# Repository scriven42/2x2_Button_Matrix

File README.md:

# 2x2_Button_Matrix

NB: I found a bug where the schematic I was using for the button was wrong, so, don't get this one yet.

As part of an ongoing project I'm not yet ready to release on here, I was looking for basic button boards I could use. And while there are several, they didn't
look like I had pictured and I didn't think they'd be comfortable to hold or use as a control. They were mostly square, and I couldn't tell the quality of the buttons
themselves or the circuitry used.

So I designed my own. It includes diodes and small capacitors for each button, to properly distinguish between buttons and allow chording.

When the code is ready to release, I'll update this to include a sample.

---
[*CC BY-SA 4.0*](https://creativecommons.org/licenses/by-sa/4.0/)

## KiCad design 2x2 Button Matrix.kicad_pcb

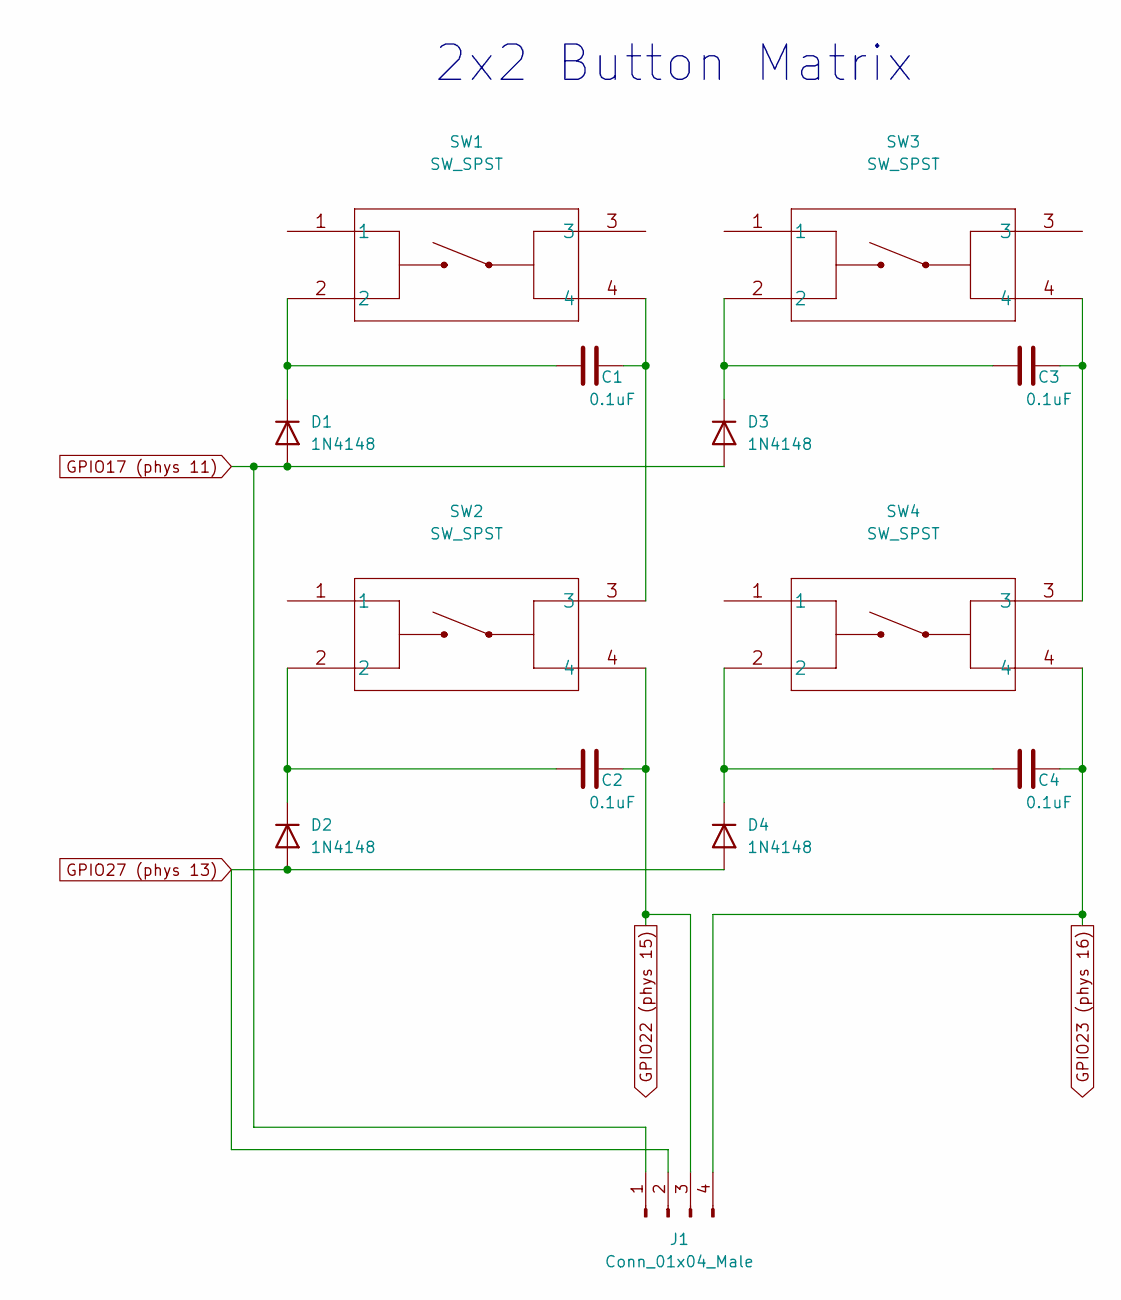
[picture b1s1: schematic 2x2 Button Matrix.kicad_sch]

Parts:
C1, C2, C3, C4: 0.1uF; C_0402_1005Metric
D1, D2, D3, D4: 1N4148; D_SOD-523
J1: Conn_01x04_Male; PinHeader_1x04_P2.54mm_Vertical
SW1, SW2, SW3, SW4: SW_SPST; 222JMVABR; MPN 222JMVABR

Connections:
GPIO17 (phys 11): D1.2 (A), D3.2 (A), J1.1
GPIO22 (phys 15): C2.2, J1.3, SW2.4
GPIO23 (phys 16): C4.2, J1.4, SW4.4
GPIO27 (phys 13): D2.2 (A), D4.2 (A), J1.2
unnamed: C1.1, D1.1 (K), SW1.2
unnamed: C1.2, SW1.4, SW2.3
unnamed: C2.1, D2.1 (K), SW2.2
unnamed: C3.1, D3.1 (K), SW3.2
unnamed: C3.2, SW3.4, SW4.3
unnamed: C4.1, D4.1 (K), SW4.2

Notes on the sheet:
2x2 Button Matrix

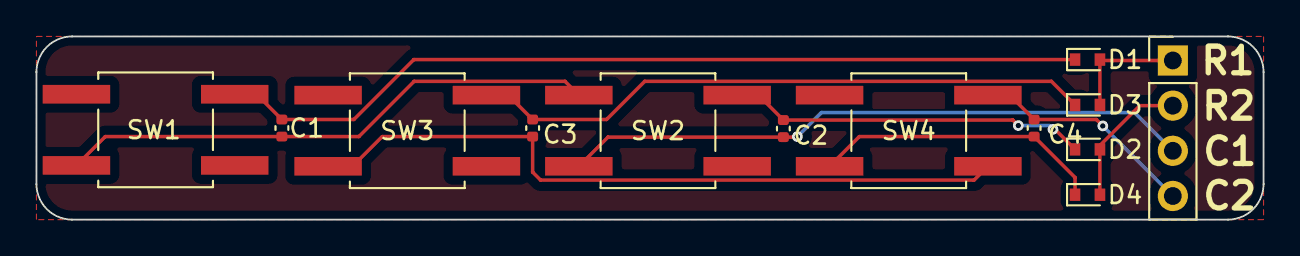
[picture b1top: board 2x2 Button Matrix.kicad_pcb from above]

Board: 2 copper layers, 69.0 x 10.3 mm, 13 parts (0 on the bottom side), 10 nets.

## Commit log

2022-07-01 Initial git commit.
2022-07-01 Added Readme.md file
2022-07-02 Added a link to the Aisler.net project
2022-07-02 Added a link to the PCBway project
2022-07-03 Update README.md
    Added link to the Creative Commons explanation
2022-07-17 Update README.md
    Found a bug in the schematic, so made a note and took out the links to the existing product.

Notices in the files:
2x2 Button Matrix.kicad_pcb:
Adam Scriven (CC BY-SA 4.0)
parts and their libraries:
Copyright 2021 Accelerated Designs. All rights reserved.
